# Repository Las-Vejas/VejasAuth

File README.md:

# VejasAuth

This is a Yubikey clone/alternative to save passkeys. I mainly made it so I could have a passkey key for the computers at my school as writing passwords is annoying.

This auth key includes:
- The RP2350 microcontroller
- 128mbit storage
- 2 buttons
- 5 GPIO outputs
- a neopixel
- a USBC port
- a USBA port

Here are some pictures / renders of it!

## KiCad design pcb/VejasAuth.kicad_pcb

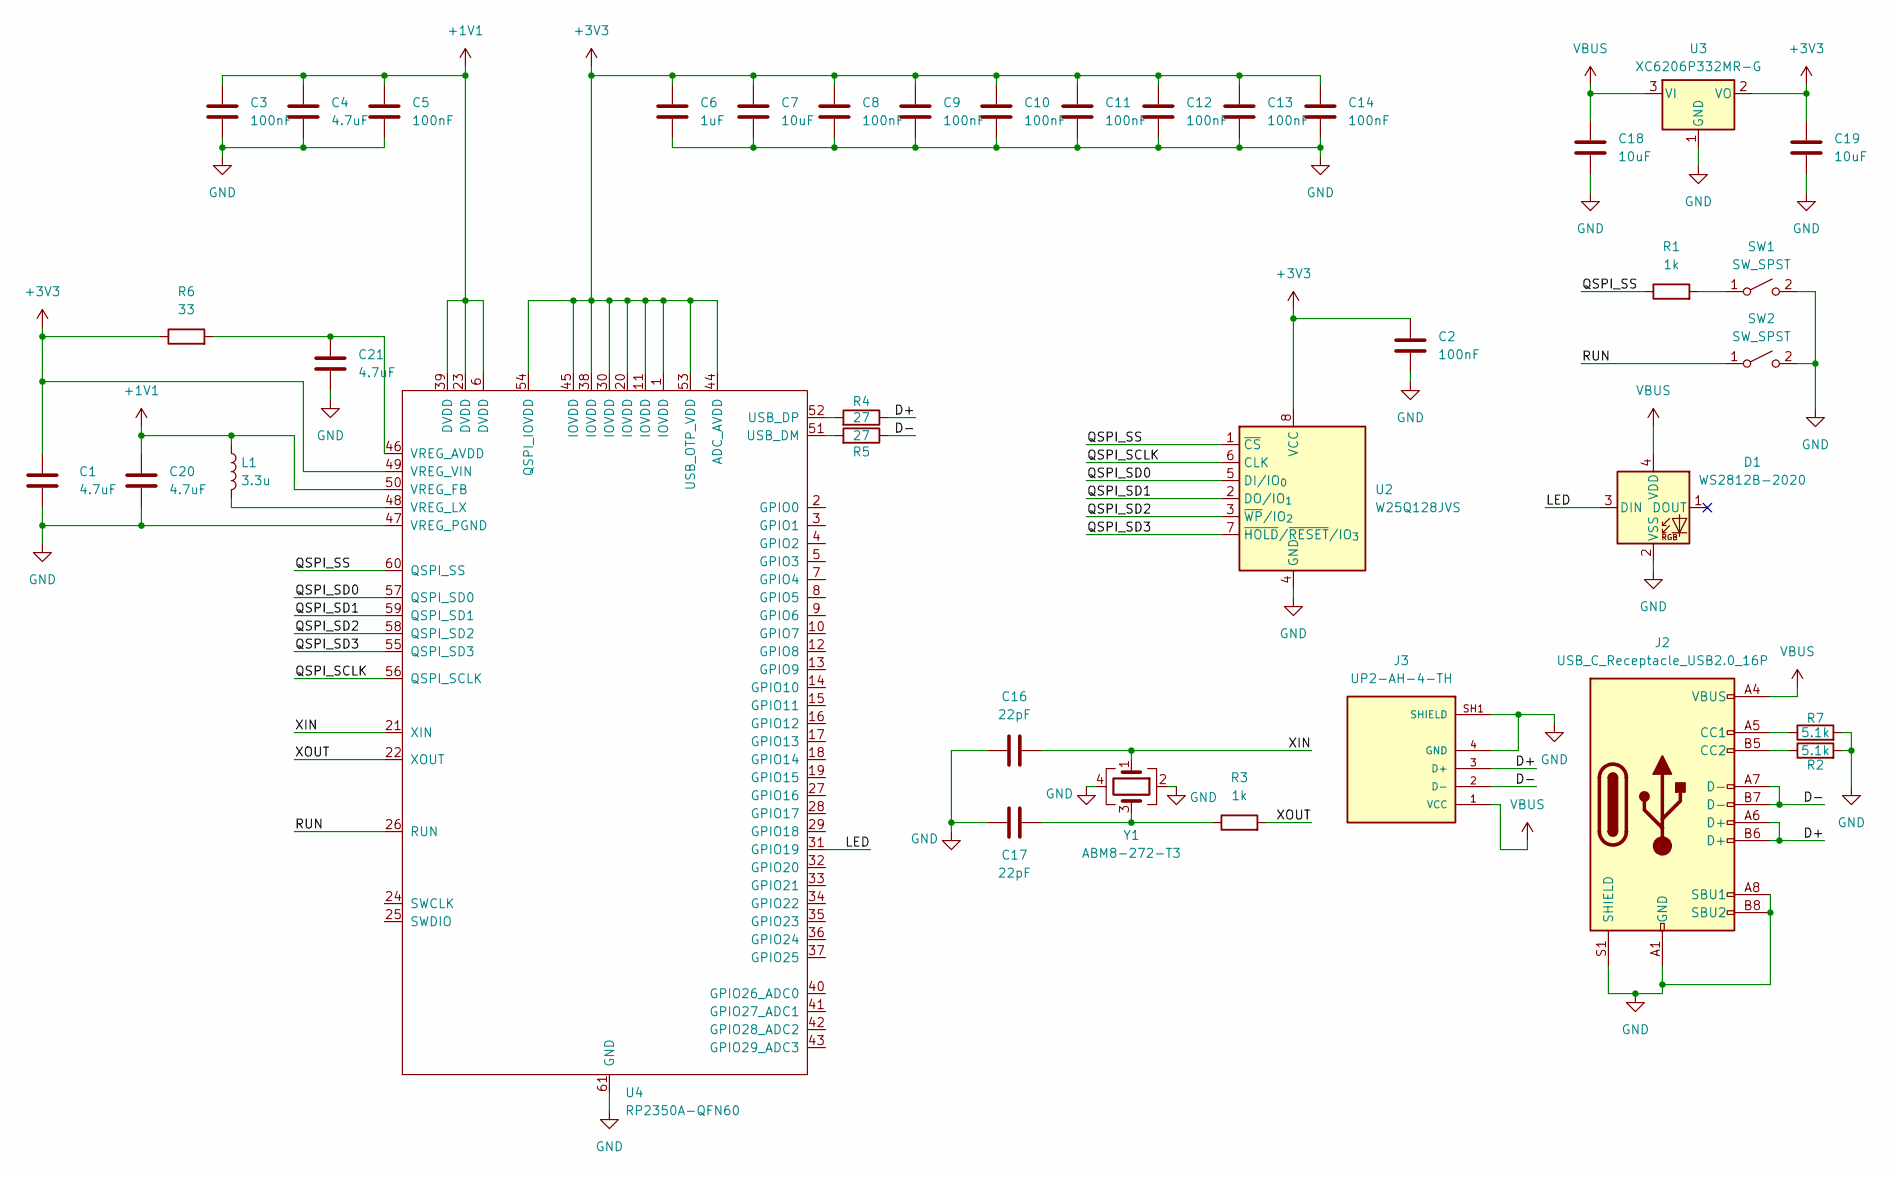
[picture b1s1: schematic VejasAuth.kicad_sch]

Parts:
C1, C4, C20, C21: 4.7uF; C_0402_1005Metric
C2, C3, C5, C8, C9, C10, C11, C12, C13, C14: 100nF; C_0402_1005Metric
C6: 1uF; C_0402_1005Metric
C7, C18, C19: 10uF; C_0603_1608Metric
C16, C17: 22pF; C_0402_1005Metric
D1: WS2812B-2020; LED_WS2812B-2020_PLCC4_2.0x2.0mm
J2: USB_C_Receptacle_USB2.0_16P; USB_C_Receptacle_GCT_USB4105-xx-A_16P_TopMnt_Horizontal
J3: UP2-AH-4-TH; CUI_UP2-AH-4-TH; PARTREV 1.05
L1: 3.3u; L_0805_2012Metric
R1, R3: 1k; R_0402_1005Metric
R2, R7: 5.1k; R_0402_1005Metric
R4, R5: 27; R_0402_1005Metric
R6: 33; R_0402_1005Metric
SW1, SW2: SW_SPST; SW_Push_SPST_NO_Alps_SKRK
U2: W25Q128JVS; SOIC-8_5.3x5.3mm_P1.27mm
U3: XC6206P332MR-G; SOT-23-3
U4: RP2350A-QFN60; QFN-60-1EP_7x7mm_P0.4mm_EP3.4x3.4mm_ThermalVias
Y1: ABM8-272-T3; Crystal_SMD_3225-4Pin_3.2x2.5mm

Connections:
+1V1: C3.1, C4.1, C5.1, C20.1, L1.1, U4.6 (DVDD), U4.23 (DVDD), U4.39 (DVDD), U4.50 (VREG_FB)
+3V3: C1.1, C2.1, C6.1, C7.1, C8.1, C9.1, C10.1, C11.1, C12.1, C13.1, C14.1, C19.1, R6.1, U2.8 (VCC), U3.2 (VO), U4.1 (IOVDD), U4.11 (IOVDD), U4.20 (IOVDD), U4.30 (IOVDD), U4.38 (IOVDD), U4.44 (ADC_AVDD), U4.45 (IOVDD), U4.49 (VREG_VIN), U4.53 (USB_OTP_VDD), U4.54 (QSPI_IOVDD)
/D+: J2.A6 (D+), J2.B6 (D+), J3.3 (D+), R4.1
/D-: J2.A7 (D-), J2.B7 (D-), J3.2 (D-), R5.1
/LED: D1.3 (DIN), U4.31 (GPIO19)
/QSPI_SCLK: U2.6 (CLK), U4.56 (QSPI_SCLK)
/QSPI_SD0: U2.5 (DI/IO_{0}), U4.57 (QSPI_SD0)
/QSPI_SD1: U2.2 (DO/IO_{1}), U4.59 (QSPI_SD1)
/QSPI_SD2: U2.3 (~WP/IO_{2}), U4.58 (QSPI_SD2)
/QSPI_SD3: U2.7 (~HOLD/~RESET/IO_{3}), U4.55 (QSPI_SD3)
/QSPI_SS: R1.1, U2.1 (~CS), U4.60 (QSPI_SS)
/RUN: SW2.1 (A), U4.26 (RUN)
/XIN: C16.2, U4.21 (XIN), Y1.1
/XOUT: R3.2, U4.22 (XOUT)
GND: C1.2, C2.2, C3.2, C4.2, C5.2, C6.2, C7.2, C8.2, C9.2, C10.2, C11.2, C12.2, C13.2, C14.2, C16.1, C17.1, C18.2, C19.2, C20.2, C21.2, D1.2 (VSS), J2.A1 (GND), J2.A8 (SBU1), J2.A12 (GND), J2.B1 (GND), J2.B8 (SBU2), J2.B12 (GND), J2.S1 (SHIELD), J3.4 (GND), J3.SH1 (SHIELD), J3.SH2 (SHIELD), R2.2, R7.2, SW1.2 (B), SW2.2 (B), U2.4 (GND), U3.1 (GND), U4.47 (VREG_PGND), U4.61 (GND), Y1.2, Y1.4
unnamed: C17.2, R3.1, Y1.3
unnamed: J2.A5 (CC1), R7.1
unnamed: J2.B5 (CC2), R2.1
unnamed: R1.2, SW1.1 (A)
unnamed: R5.2, U4.51 (USB_DM)
unnamed: R4.2, U4.52 (USB_DP)
unnamed: C21.1, R6.2, U4.46 (VREG_AVDD)
unnamed: L1.2, U4.48 (VREG_LX)
VBUS: C18.1, D1.4 (VDD), J2.A4 (VBUS), J2.A9 (VBUS), J2.B4 (VBUS), J2.B9 (VBUS), J3.1 (VCC), U3.3 (VI)

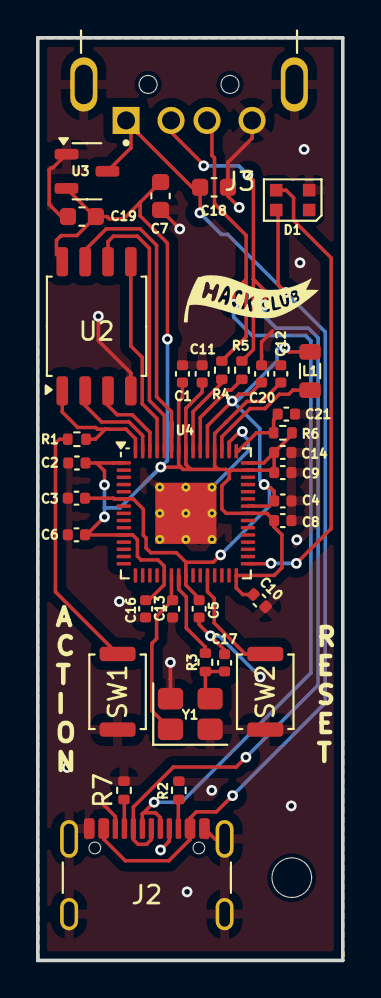
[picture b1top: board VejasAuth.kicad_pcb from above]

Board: 2 copper layers, 16.9 x 51.3 mm, 37 parts (0 on the bottom side), 24 nets.

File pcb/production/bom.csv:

Designator,Footprint,Quantity,Value,LCSC Part #
"C1, C20, C21, C4",0402,4,4.7uF,
"C10, C11, C12, C13, C14, C2, C3, C5, C8, C9",0402,10,100nF,
"C16, C17",0402,2,22pF,
"C18, C19, C7",0603,3,10uF,
C6,0402,1,1uF,
D1,LED_WS2812B-2020_PLCC4_2.0x2.0mm,1,WS2812B-2020,
J2,USB_C_Receptacle_GCT_USB4105-xx-A_16P_TopMnt_Horizontal,1,USB_C_Receptacle_USB2.0_16P,
J3,CUI_UP2-AH-4-TH,1,UP2-AH-4-TH,
L1,0805,1,3.3u,
"R1, R3",0402,2,1k,
"R2, R7",0402,2,5.1k,
"R4, R5",0402,2,27,
R6,0402,1,33,
"SW1, SW2",SW_Push_SPST_NO_Alps_SKRK,2,SW_SPST,
U2,SOIC-8_5.3x5.3mm_P1.27mm,1,W25Q128JVS,
U3,SOT-23-3,1,XC6206P332MR-G,
U4,QFN-60-1EP_7x7mm_P0.4mm_EP3.4x3.4mm_ThermalVias,1,RP2350A-QFN60,
Y1,Crystal_SMD_3225-4Pin_3.2x2.5mm,1,ABM8-272-T3,

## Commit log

2025-10-12 schem
2025-10-14 Enhance README with project details and features
    Added project description and features to README.
2025-10-14 pcb1.0
2025-10-14 pcb1.1
2025-10-14 pcb1.1.1
2025-10-14 prod
2025-10-24 cool stuff V1 i think
2025-12-07 Enhance README with images and project details
    Added images and additional details about the project.
2026-01-21 big update
2026-01-21 upd bom
